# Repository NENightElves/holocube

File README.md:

# holocube

# Libraries

-   https://github.com/russhughes/st7789_mpy

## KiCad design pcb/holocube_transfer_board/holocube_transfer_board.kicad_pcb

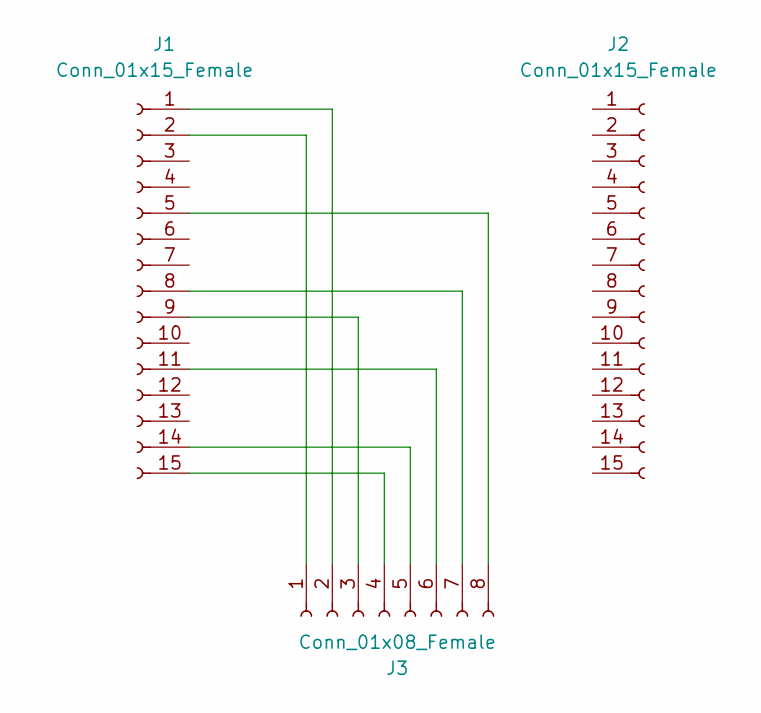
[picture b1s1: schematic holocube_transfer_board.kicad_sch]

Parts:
J1, J2: Conn_01x15_Female; PinSocket_1x15_P2.54mm_Vertical
J3: Conn_01x08_Female; PinSocket_1x08_P2.54mm_Vertical

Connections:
unnamed: J1.1, J3.2
unnamed: J1.2, J3.1
unnamed: J1.8, J3.7
unnamed: J1.9, J3.3
unnamed: J1.11, J3.6
unnamed: J1.14, J3.5
unnamed: J1.15, J3.4
unnamed: J1.5, J3.8

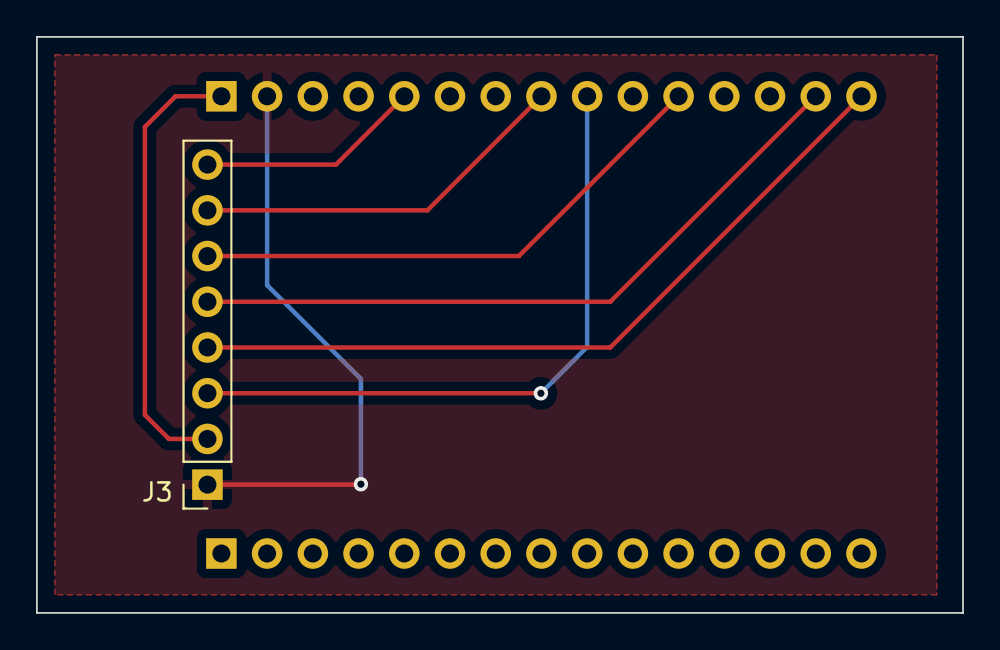
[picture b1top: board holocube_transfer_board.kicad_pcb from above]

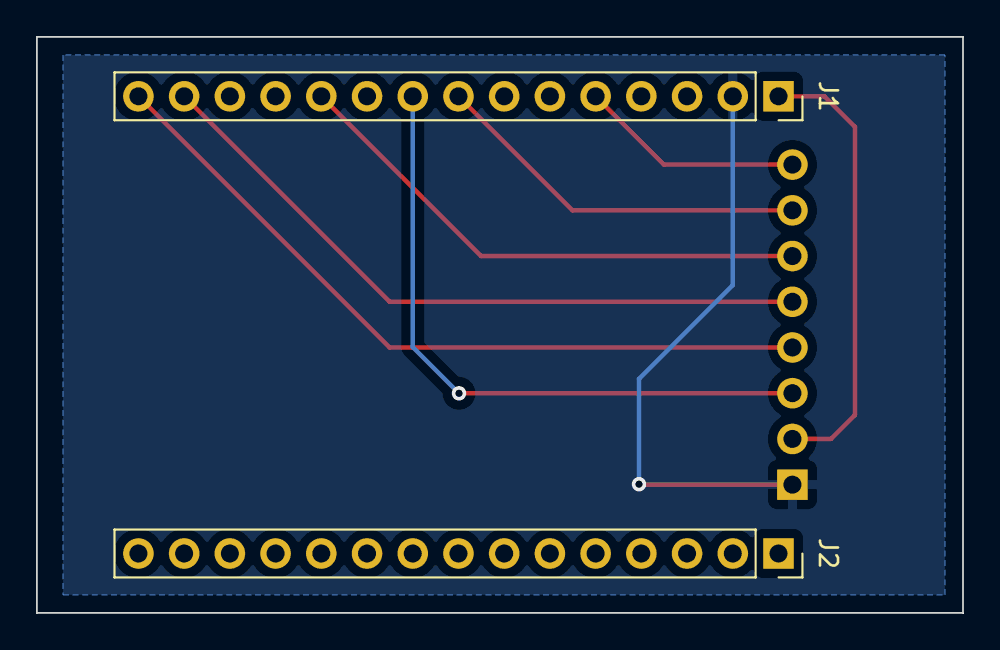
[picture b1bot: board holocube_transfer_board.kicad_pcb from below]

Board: 2 copper layers, 51.5 x 32.0 mm, 3 parts (2 on the bottom side), 8 nets.

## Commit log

2021-12-31 add Pin_Location.md
2021-12-31 add pcb holocube_transfer_board
2022-01-01 update holocude_transfer_board
2022-01-08 add outer_shell model
2022-01-09 init upload
2022-01-09 add gitignore
2022-01-09 update ntp
